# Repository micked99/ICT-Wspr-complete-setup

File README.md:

## Updates
20261018  <br>
Changed Timing.h so it will not wait for its 10 min schedule, if the board starts at any minute inside the scheduled time it will starta at next 2 min window to tx a standard wspr packet and then resume the order of schedule you have set.

20261017  <br>
Major overhaul of the code, biggest enhancements is the mergin of the 180° tx code with the normal tx code with a setting to run the board in standard - normal (true/false flag) dipole mode or in 180° mode with the dipole halfs fed 180° antiphase, quadruple the power output but only doubling the power consumption of the si5351 - in theory. Power demands increase from 25mA in dipole to 30mA 180 degree mode, also lots of old unused code mainly the jt9 codesnips that was left in there removed, all user configureble  settings moved to one place in the beginning of the .ino file - new and old pcb:s 100% compatible but old pcb:s does not have clk1 routed that is needed for 180° tx so only dipole mode works on them. (si5351 use about 17mA in stb and 27mA in tx using clk0 + 5mA for clk1.) <br>
Bugfix: if slot on minute 8 was used in previous fw it jumped a 10min seq before it started tx again - now been fixed <br>

Fixed a bug in telemetry/gps data and moved all configurable settings into the .ino file, like channel and tcxo freq

A 180° tx with a 4x power output avalible here: https://github.com/micked99/ICT-wspr-180-4x-the-power-output

BOM and Pick and place files added if you want to for example JLCPCB to make and assamble the complete board  

BOM_ict_v361-xs.csv & CPL_pick place_ict_v361-xs.xlsx  

Screenshots of the settings of order of pcb assembly, see folder "JLCPcb order"  

Get your board online onto Sondehub/aprs.fi section added  

# ICT-v7-ATGM336
  <br> <br>

## Introduction
This FW is mostly the work of Eduard YO3ICT,  you can read about here: https://yo3ict.uus.ro/tracker.html  
What I have done is to simplify it even more with a few less components and a slightly easier to solder pcb.

What Eduard did was reverse enginer the [QRP-Labs](https://shop.qrp-labs.com) telemetry protocol which use wspr to get data through, and open sourced it, details of the protocol is described here: https://qrp-labs.com/flights/s4#protocol 
most balloons use this encoding today, with a few exceptions, like [Zachtek](https://www.zachtek.com)  

Another good site for beginers is to read up and join the io board at: https://groups.io/g/picoballoon 

The [Traquito](https://traquito.github.io/)  page will host channel reservation and upload to varous tracking sites like https://aprs.fi/ and https://amateur.sondehub.org/ and as well host its own map, more maps and info avalible here https://lu7aa.org/dx.asp and here http://qrp-labs.com/tracking.html, another good page that poped up lately is [wsprtv](https://wsprtv.com/docs/user_guide.html#u4b-channel-map) & [wsprtv channel map](https://wsprtv.com/tools/channel_map.html?band=17m&num_days=30&rx_threshold=1)

##
## --Everything in this git is in Metrics--
##

## Folders in this repo:  
### ICT_WSPR   
The Arduino code to upload to the PCB  
### Libraries
Copy the content in this folder into libraries folder of Arduino C:\Program Files (x86)\Arduino\libraries  
### Pcb-ICT-main  
Cam files for pcb ordering as well as the Eagle schematic and board files, viewer for both files here: https://www.altium365.com/viewer/
### Boards.txt-main  
Replace the Boards.txt in arduino to controll the speed of the 328, its located in: C:\Program Files (x86)\Arduino\hardware\arduino\avr  

## Goals  
This setup is aimed at three main things: light weight, low power demands and as few components as possible - easy to build

The board can be built to weigh below 1 gram fully assembled (pic below) with solar cells & antenna connected total weight 4-5 gram

To make the board consume as little power as possible its setup to switch between tx and gps so only one of the two is ON at any time, so it will startup and get valid gps lock with tx side of the board switched off, the tx ic - si5351 consumes 17-27mA (depending on model) in stb curent even when not in use so only the gps is on and draws about 25mA using the ATGM336 (N31), when the board have got a valid lock the gps will turn off and the wspr tx starts, it will be about 30mA, on top of this the 328 running at 2Mhz and the Tcxo combined will take another 3mA 

The board will work on any band between 14Mhhz and 28Mhz

# Features  
CW init - At power on, when sun hits the solar panels it start to tx cw, then you know you are good for launch  
No tx over selected grids - Move tx to ism (13.555) freq over selected grids  
Powerswitching between gps and tx - Will put less stress on the cells and get earlie in the morning startups  
Course altitude in main wspr - Will insert a rough altitude into the standard wspr db field, see TelemFunctions.h  
Good WDT function of 328 - Will never fail to wake up even with unstable solar cells powering the board  
Will work at low clocks, tested down to 1Mhz on the 328 - Deafult is 2Mhz  
Powersave of gps by set it to single navigational system  - See Gps section  

# GPS:

The ATGM336-N31 support both GPS and Beidou system, by switching off Beidou and run the ATGM in GPS only mode we save about 4mA, see .ino file for the command, gps only is activated by default.  
This gps does not have any altitude limit like many other modules, its been tested to 150.000m with a hack-rf and GPSSim and still worked fine

## BOM

All components but the si5351 is bought on Aliexpress, you can source the SI535/MS5351 on Ali but they can have an higher power consumption then the original, from my experience the Ali ones draw 27mA instead of 17mA in stb current of the genuine ones 
----------------  
Cpu ATmega328P (328PB also works but need installing MiniCore in Arduino IDE)

Gps ATGM336 (N31) others will work  

TX Si5351  

Tcxo 25/26/27 Mhz size 3225 3.2x2.5mm  

Xo 4Mhz size 4520 4.5mm×2mm   

2x 10K resistor size 0603, value non critical, 1K-10K works  

2x 100nF Capacitor size 0603, value non critical 10-470nF works, it will work fine without any soldered on but I recommend at least one  

2.54mm x2 Pin Header - Remove before flight by cutting it of with a scissor  

# Antennas

For gps antenna use a 46mm wire which represents a 1/4 antenna at 1575Mhz  

For tx antenna I use 0,15mm which is a good combination of strength and weigh but any wire in the 0,1 - 0,2mm will work fine, try enameled copper wire that is heatstrippable

I use a small hook 2cm long made of 0,6mm wire bottom, and 0,8mm at the top to solder on the antenna wire, solder and twist a couple of turns arround the hook  
  <br>  
Here is good picture where you can see the Red and Yellow gps antennas  
  <br>  

Tx Antenna length calculated as normal, 300/freq x 0.95 /4 

Upper antenna leg should be supported by a fishing line taped between the balloon and pcb

# Solar cells

6 psc of solar cells connected in series will work fine, or 4 psc of a bit larger cells and a voltage doubler with 3,3V ldo like REG710 will do the work, ready made pcb are avalible on Aliexpress, search for "Low Noise Regulated Charge Pump" see below pic  
  <br> 

Do not try use converters with an inductor, they will not work, only converters using a capacitor are likeley to succeed.  

As can be seeen in the below picture the solar cells is intended to be soldered to the board with a center copper rod of 0,8mm, notice,  
there are two pairs of vias, one is GND and one pair is not connected to anything which is where you solder the center support for the cells - see below pic  
  <br>  
OBS! The programming pinhead should be cutoff before flight and preferably before you solder the cells onto the pcb  

 <br> 
Solderpoints for the solar cells  

With 6 x 38x19 cells ounded flat you can see a startup of the board at about 13° solar angle 

How I solder the cells together, I use a 0,6mm wire I extract from a multi stranded electrical cable, and then a very thin wire from an even smaller multi stranded cable to solder the cells to the pcb, pics:

  <br>  
  <br>  

To test the solar + board indoor before a flight you can use a Halogen flood light like below pic, I use a 400W, 8545 lumen lamp.  
-OBS- Led lamps wont work.

  <br>  

# Arduino

To compile and upload the sketch I use Arduino version 1.8.13 which you find here, others will work but not tested, <br> https://www.arduino.cc/en/software/OldSoftwareReleases/<br> 
Resently tested last version as of now 2.3.10 which also worked fine.

# 328 Fuses

Sets the expected external or internal xo used and also set the brownout to 1,8V

The 328 have an internal xo at 8Mhz, you can set it to be divided down by 8 (fuse) and then the board runs at 1Mhz
the internal xo at 8Mhz is not very stable in cold and it will not work at flying altitude, but I have tried a few flights on the internal xo divided down to 1Mhz 
and it have worked fine, anyway, both speeeds works fine for testing a board on the bench, but I do recomend that you use the suggested 4Mhz xo as in the schematic.

FD D9 FE 1,8V / External 2/4/8Mhz xo, Brownout to 1,8V - This is the fuses you should use if you build this board  

62 D9 FE 1.8V / internal 8Mhz osc /div8 = 1Mhz  
E2 D9 FE 1.8V / internal 8Mhz osc  

To set fuses use Avrdudess https://github.com/ZakKemble/AVRDUDESS

Fusecalc page https://www.engbedded.com/fusecalc/

I would recommend to buy a couple of arduino nano boards to practice on before flashing fuses onto a built board, as this is the main culprit of non responsive 328 - wrongly set or corrupted fuses

# Programming

The pcb is fited with a 6 pin ISP connector  
The Arduino uploads the fw with an USBasp programmer, get a 3,3v version with a 10 to 6 pin header adapter on the end of the ribbon cable  
To upload a .hex file like the one supplied in oscillator-main folder I recommend using AVRDUDESS - A GUI for AVRDUDE

https://blog.zakkemble.net/avrdudess-a-gui-for-avrdude/  
https://github.com/avrdudes/avrdude/  

Use libsusbK in Zadig to install driver for the Usbasp: https://zadig.akeo.ie/

  <br>  

In Arduino IDE select Usbasp as programmer:    
  <br>

In Boards select rAVA 2Mhz:    
  <br>  
# PCB  

  <br>  

I have always used Jlcpcb at https://jlcpcb.com/ for my balloon boards and other projects

The pcb files have been made with Eagle pcb nowadays under the name Autodesk Eagle https://www.autodesk.com/products/eagle/overview

Make the PCB as thin as possible to save weight, 0,6mm is good compromise between weight and price

In Pcb-ICT-main folder in this repo you will find needed CAM files in the zip´s, if you are a experieced with solder small parts and have a hot air solder station go with the Xtra Smal QFN version (ict_v361-xs.zip) of the board, for a more simple soldering setup use the TQFP version (ict_v361.zip)

Here is what a JLC-PCB assambled board looks like, pictures from Michael KC3GMG  

# Schematic  

# Setup parameters in the code  
The Arduino code is setup from start to use a 26Mhz Tcxo and a 4Mhz crystal, if other values used the code needs to be changed - see below  

Values to edit in the ino file  <br>

<br>

const char call[] = "SA7BSS";      // WSPR Standard callsign -- SA7BSS for bench testing, SA6BSS for flight<br>
char tlm_channel1 = '1';           // Telemetry channel: 0/1/Q<br>
char tlm_channel2 = '1';           // Telemetry channel: 0-9<br>
const uint32_t tcxo  = 26000000UL; // TCXO/crystal frequency in Hz<br>
const bool use180deg = false;      // Hardware config: true = 180° dipole (CLK0+CLK1), false = standard/ground-wire (CLK0)<br><br>
 
See this page for channel setup and reservation: https://traquito.github.io/channelmap/ & https://wsprtv.com/tools/channel_map.html

CW setup, the board will at first moment at power on send a morse signal with your callsign<br>
This is a first good test the board is working, set the freq in Beep.h, it will beep without a gps soldered
Here is my SA6BSS call in the ino file  <br>
cw_s(); cw_a(); cw_6(); cw_b(); cw_s(); cw_s();  <br>

Testing and Scheduling of tx sequence<br>

After power on it will beep a cw for 5 sec then switch over to gps that takes about 25-30sec to get a GPS fix if in clear sky or gps repeater used, GPS through a window can take 1-2 minutes.

Edit Timing.h sceduling at what minute you want to tx your normal wspr and at what minute to tx the telemetry, this can be done inside Arduino ide or with a normal texteditor, this is self explanatory

const uint8_t TX_SLOTS  = SLOT(0) | SLOT(2) | SLOT(6) | SLOT(8);  // minutes that transmit; any other even minute is idle (GPS only)<br>
const uint8_t TLM_SLOT  = 2;   // minute that carries the telemetry message (must be one of TX_SLOTS)<br>
const uint8_t PREP_SLOT = 6;   // minute where new GPS data is read (the first TX slot after the idle one)<br>

"PREP_SLOT = 6; "This can be a bit unlogical but its the first tx after the GPS got new data, we can see "TX_SLOTS  = SLOT(0) | SLOT(2) | SLOT(6) | SLOT(8); " where 4 is the slot where the radio switch off and the gps enables, so PREP_SLOT = 6; is the first slot after gps got new data into the board

To adjust the sequence in what order the standard and telemtry is transmitted edit Timing.h, it is set to transmitt 4 times - 8 minutes and then switching off the radio and enable gps, gets new loction data, then start over.

##

This is the standard setup using a 4 Mhz xo, so if you build the board with the recommended components and downloaded fw this does not need to change
Sets speed of the board  
clock_prescale_set(clock_div_2);  or clock_prescale_set(clock_div_4);  
this in conjuction with:    
#define WSPR_CTC 1334  
and select rAVA 2Mhz from boards in Arduino boards 

Alternative clocksettings:  
WSPR CTC - 2668 @ 4Mhz //1334 @ 2Mhz //667 @ 1Mhz  
And to select the appropriate board setting under Boards in Arduino,  
lets say we want to set the board to 1Mhz using a 4Mhz xo we need to set the prescaler to  
clock_prescale_set(clock_div_4);   
and set  
WSPR CTC 667  
and then select gAVA 1Mhz under boards, see section Programming  

then, for example if you wan to run it a 4Mhz set:
WSPR CTC - 2668  
mark out both of the //clock_prescale_set  
and use hAVA 4Mhz board setting  

to set cw tx frequncy adjust it in Beep.h, this will tx a short cw init as soon as you connect power<br>
     freq = 14096980UL;  <br>
  // freq = 18105900UL;  <br>
  // freq = 28125870UL;  <br>

# Balance the board

You want the board to be as leveled as possible so the solarcells always points up and not to the sides,  
to do this use the top hook, puti it on a short loop of fishing line and bend the copper rod untill it levels up, see below:  

  <br> 

# Get your flight uploaded to Sondehub and/or aprs.fi

There is a couple of ways to get your board onto [Sondehub](https://amateur.sondehub.org/) 

The way Im doing it is to use a wspr-to-sondehub python script described here: https://github.com/micked99/wspr-to-sondehub-script
What I do is to use this script with a filtering function so your upload data dont get mixed with other flights - you should check the channel is free here before relesing a balloon:  [WSPR-TV](https://wsprtv.com/tools/channel_map.html?band=17m&num_days=30&rx_threshold=1) but as the 600 channels per band is relaying on filtering on frequency and this script cant handle that, this is a simple workarround.
So the idea I got and that DG4NOB implemented in the python upload code was that we can use the voltage reading of the battery as a filtering function, as we use solar cells, voltage is mostly of no interest, reading the Encoding [Description](https://qrp-labs.com/flights/s4#protocol) we see "Battery voltage is coded by a number in the range 0..39, which represents battery voltage in the range 3.00 to 4.95V with a resolution of 0.05V" this means we have 40 unique "channels" within this, so what we can do is to set a static value in the ict fw and uplod this to the board, <br> 
look at lines 126 - 132 in TelemFunctions.h and you see this:<br> 

  sensorVolt = sensorVolt / 5;   // mark out for fixed voltage<br> 
  volt = sensorVolt * 1.1f;      // mark out for fixed voltage<br> 
  volt = volt / 1023.0f;         // mark out for fixed voltage<br> 
  volt = volt * 4.18f;           // mark out for fixed voltage<br> 
  // volt = 3.94;                // --Remove if sensor voltage is used--<br>
  if (volt < 3.0) volt = 3.0;    // mark out for fixed voltage<br>
  if (volt > 4.95) volt = 4.95;  // mark out for fixed voltage<br>   

The normal setup is as above where the adc reads the voltage on sensorpin, it should be a voltage divider there but I have routed the pin directly to vcc so if you dont make any edits to the code it will constantly read 4.56V, so what we can do is to change the code, say we want to filter the voltage to 3,94V we edit the code to:  

 // sensorVolt = sensorVolt / 5;   // mark out for fixed voltage<br>
 // volt = sensorVolt * 1.1f;      // mark out for fixed voltage<br>
 // volt = volt / 1023.0f;         // mark out for fixed voltage<br>
 // volt = volt * 4.18f;           // mark out for fixed voltage<br>
    volt = 3.94;                   // --Remove if sensor voltage is used--<br>
 // if (volt < 3.0) volt = 3.0;    // mark out for fixed voltage<br>
 // if (volt > 4.95) volt = 4.95;  // mark out for fixed voltage<br>

After we done this and upload the code to the pcb we should have a fixed voltage reading constantly sending 3,94V which we can put in the balloon.ini file in the  [wspr upload script](https://github.com/micked99/wspr-to-sondehub-script)  

If you have launched the board with no editing to the ict code you can set 4,56V as a filter, this making it work on boards allready in flight.  

You need to double check the voltage readign your board actually tx as there will be a 0,01V variation on the actual value that comes out of the decoder, even if you set 3,94V it might be 3,95 that comes out, you can test it in this xls  
https://qrp-labs.com/images/ultimate3builder/ve3kcl/s4/308d.xls  
originating from https://qrp-labs.com/flights/s4#protocol  

Other ways to get you board online is to use https://lu7aa.org.ar/wsprset.asp  

There is also an uploader by Bill WB8ELK - maker of [Skytracker](https://elktronics.com) that you can download from [Here](https://groups.io/g/picoballoon/message/23150?p=%2C%2C%2C50%2C0%2C0%2C0%3A%3Arecentpostdate%2Fsticky%2C%2Cwspr2aprs%2C50%2C2%2C0%2C114107378)  
You need to be a member of this io board to access it, it will upload to aprs.fi and Sondehub will then automaticly pipe it onto its site,  
pros of this program is easy to setup and it can filter on Frequency as the 600 channel mapping require.  

# Misc pictures

  <br> 
  <br>

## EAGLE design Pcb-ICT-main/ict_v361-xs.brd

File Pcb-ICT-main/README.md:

# ICT-PCB

Eagle PCB for my modified version of the ICT wspr setup 

This pcb is made and setup for my current version of the the ict code

ict_v361-xs // Extra small, using the QFN/MLF version of the 328 - Verified working

ict_v361 // Normal size, using the TQFP version of the 328 - untested but should work

Use .zip files for pcb ordering

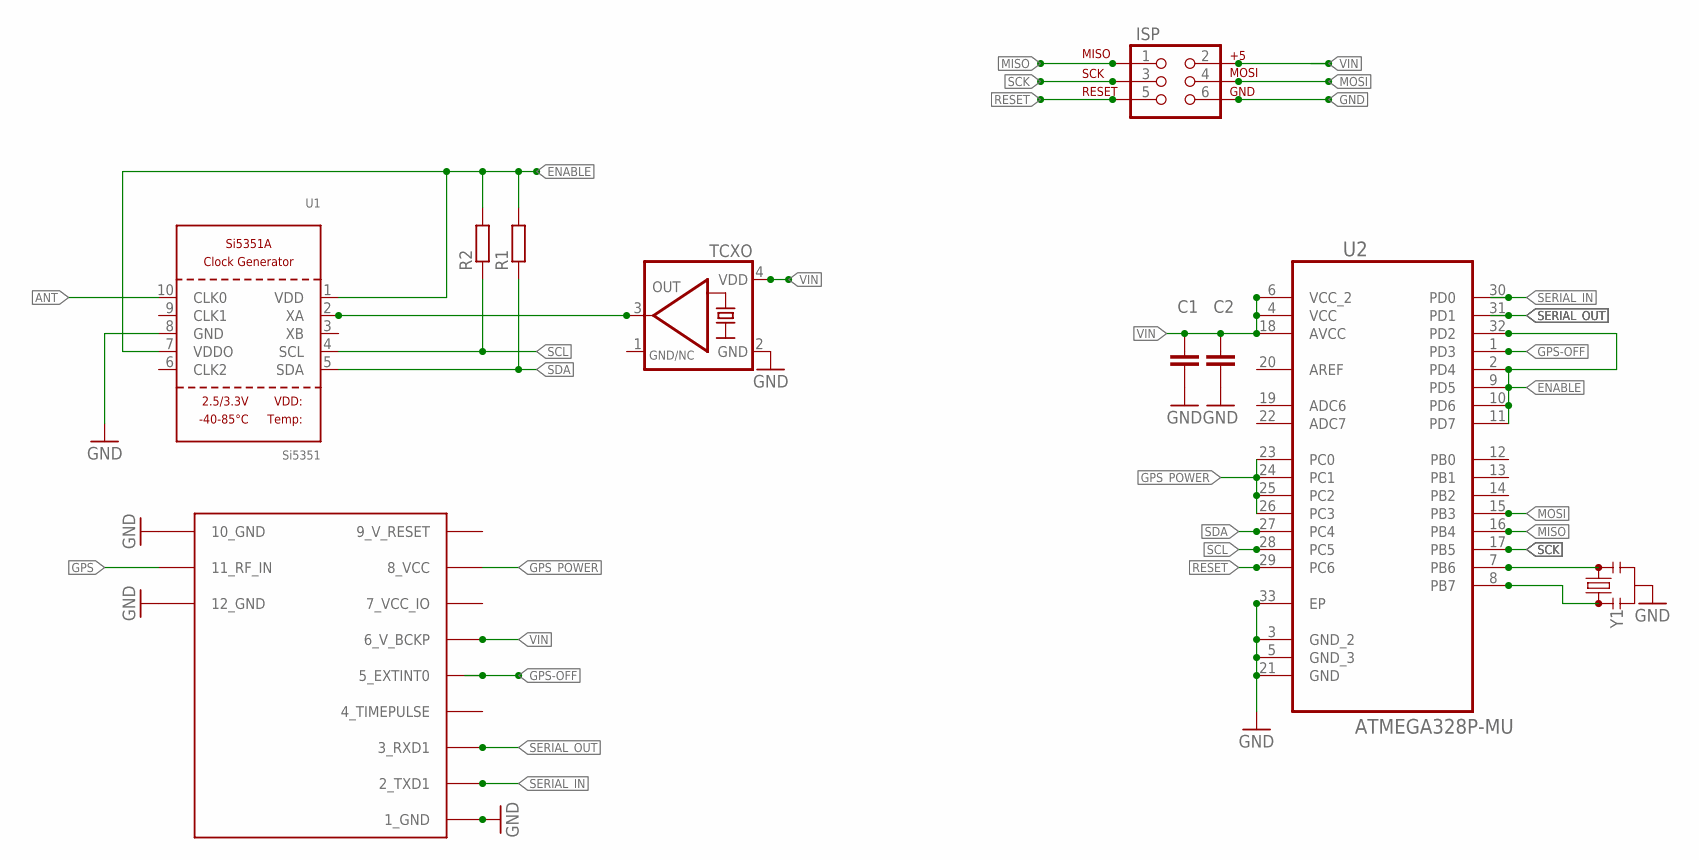
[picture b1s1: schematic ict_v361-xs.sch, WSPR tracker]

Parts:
C1, C2: C-EUC0603K; C0603K
GPS: UBLOX_MAX
ISP: AVR_SPI_PRG_6PTH; 2X3
R1, R2: R-EU_R0603; R0603
TCXO: KXO-TCXO-CMOS-84; 3.2X2.5_KXO-84-TCXO
U1: Si5351; MSOP10
U2: ATMEGA328P-MU; QFN50P500X500X100-33N
Y1: RESONATORSMD-4.5X2.0; RESONATOR-SMD-4.5X2.0

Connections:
7_VCC_IO: GPS.7_VCC_IO
9_V_RESET: GPS.9_V_RESET
ANT: U1.10 (CLK0)
ENABLE: R1.2, R2.2, U1.1 (VDD), U1.7 (VDDO), U2.2 (PD4), U2.9 (PD5), U2.10 (PD6), U2.11 (PD7), U2.32 (PD2)
GND: C1.2, C2.2, GPS.1_GND, GPS.10_GND, GPS.12_GND, ISP.6, TCXO.2 (GND), U1.8 (GND), U2.3 (GND_2), U2.5 (GND_3), U2.21 (GND), U2.33 (EP), Y1.2
GND/NC: TCXO.1 (GND/NC)
GPS: GPS.11_RF_IN
GPS-OFF: GPS.5_EXTINT0, U2.1 (PD3)
GPS_POWER: GPS.8_VCC, U2.23 (PC0), U2.24 (PC1), U2.25 (PC2), U2.26 (PC3)
MISO: ISP.1, U2.16 (PB4)
MOSI: ISP.4, U2.15 (PB3)
unnamed: U2.7 (PB6), Y1.3
unnamed: U2.8 (PB7), Y1.1
unnamed: TCXO.3 (OUT), U1.2 (XA)
RESET: ISP.5, U2.29 (PC6)
SCK: ISP.3, U2.17 (PB5)
SCL: R2.1, U1.4 (SCL), U2.28 (PC5)
SDA: R1.1, U1.5 (SDA), U2.27 (PC4)
SERIAL_IN: GPS.2_TXD1, U2.30 (PD0)
SERIAL_OUT: GPS.3_RXD1, U2.31 (PD1)
VIN: C1.1, C2.1, GPS.6_V_BCKP, ISP.2, TCXO.4 (VDD), U2.4 (VCC), U2.6 (VCC_2), U2.18 (AVCC)

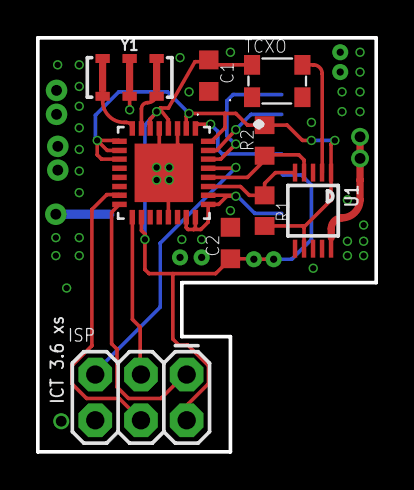
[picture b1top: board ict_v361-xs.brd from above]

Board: 2 copper layers, 18.8 x 23.0 mm, 10 parts (1 on the bottom side), 16 nets.

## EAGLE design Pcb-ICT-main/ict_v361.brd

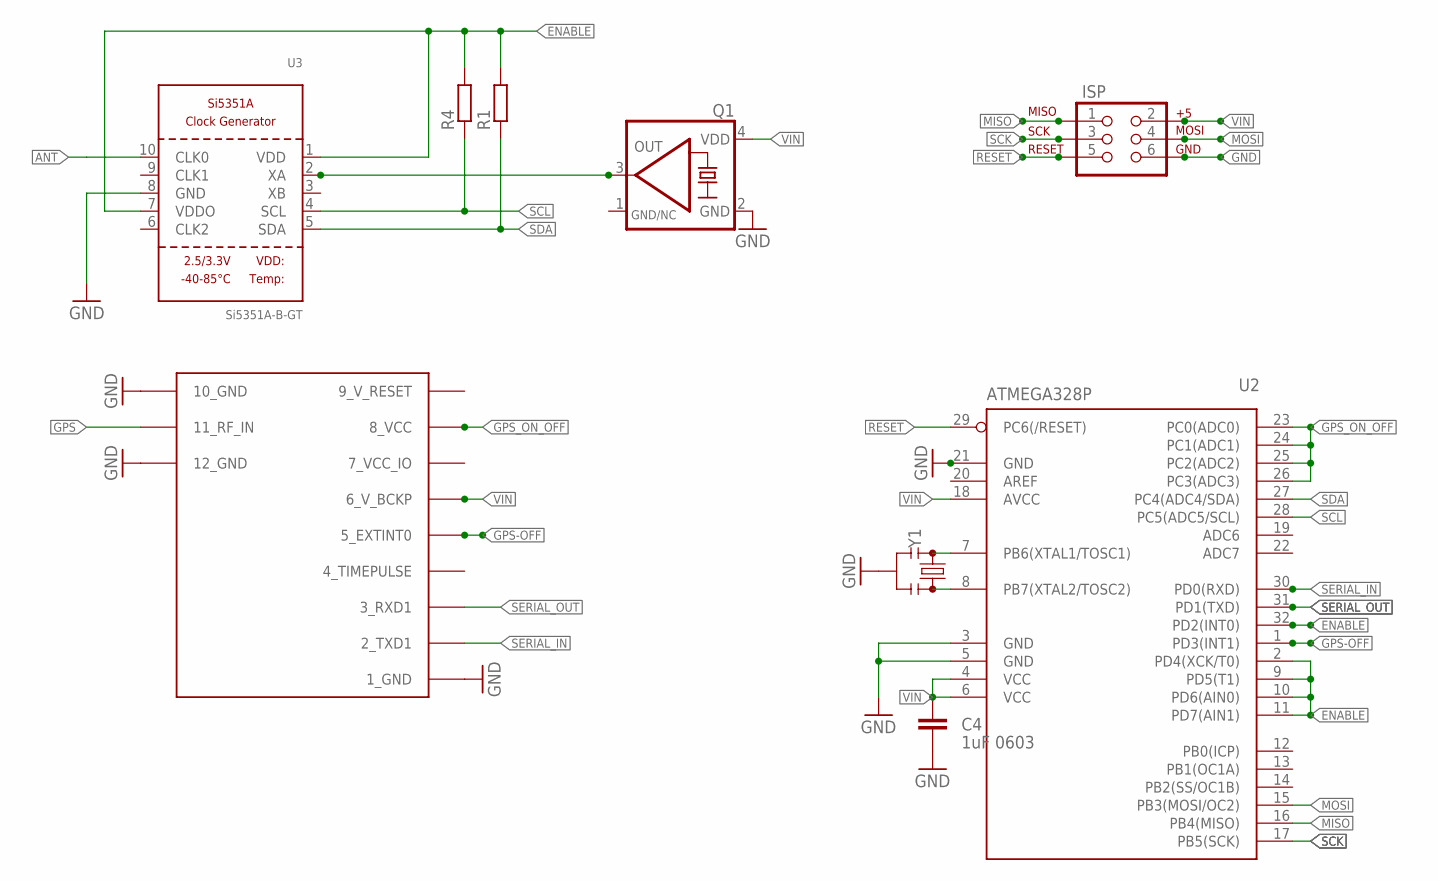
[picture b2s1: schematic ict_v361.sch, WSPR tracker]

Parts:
C4: 1uF 0603; C0603K
ISP: AVR_SPI_PRG_6PTH; 2X3
Q1: KXO-TCXO-CMOS-84; 3.2X2.5_KXO-84-TCXO
R1, R4: R-EU_R0603; R0603
U2: ATMEGA328P; TQFP32-08
U3: Si5351A-B-GT; MSOP10
U$2: UBLOX_MAX
Y1: RESONATORSMD-4.5X2.0; RESONATOR-SMD-4.5X2.0

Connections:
7_VCC_IO: U$2.7_VCC_IO
9_V_RESET: U$2.9_V_RESET
ANT: U3.10 (CLK0)
ENABLE: R1.2, R4.2, U2.2 (PD4(XCK/T0)), U2.9 (PD5(T1)), U2.10 (PD6(AIN0)), U2.11 (PD7(AIN1)), U2.32 (PD2(INT0)), U3.1 (VDD), U3.7 (VDDO)
GND: C4.2, ISP.6, Q1.2 (GND), U2.3 (GND), U2.5 (GND), U2.21 (GND), U3.8 (GND), U$2.1_GND, U$2.10_GND, U$2.12_GND, Y1.2
GND/NC: Q1.1 (GND/NC)
GPS: U$2.11_RF_IN
GPS-OFF: U2.1 (PD3(INT1)), U$2.5_EXTINT0
GPS_ON_OFF: U2.23 (PC0(ADC0)), U2.24 (PC1(ADC1)), U2.25 (PC2(ADC2)), U2.26 (PC3(ADC3)), U$2.8_VCC
MISO: ISP.1, U2.16 (PB4(MISO))
MOSI: ISP.4, U2.15 (PB3(MOSI/OC2))
unnamed: U2.8 (PB7(XTAL2/TOSC2)), Y1.3
unnamed: U2.7 (PB6(XTAL1/TOSC1)), Y1.1
unnamed: Q1.3 (OUT), U3.2 (XA)
RESET: ISP.5, U2.29 (PC6(/RESET))
SCK: ISP.3, U2.17 (PB5(SCK))
SCL: R4.1, U2.28 (PC5(ADC5/SCL)), U3.4 (SCL)
SDA: R1.1, U2.27 (PC4(ADC4/SDA)), U3.5 (SDA)
SERIAL_IN: U2.30 (PD0(RXD)), U$2.2_TXD1
SERIAL_OUT: U2.31 (PD1(TXD)), U$2.3_RXD1
VIN: C4.1, ISP.2, Q1.4 (VDD), U2.4 (VCC), U2.6 (VCC), U2.18 (AVCC), U$2.6_V_BCKP

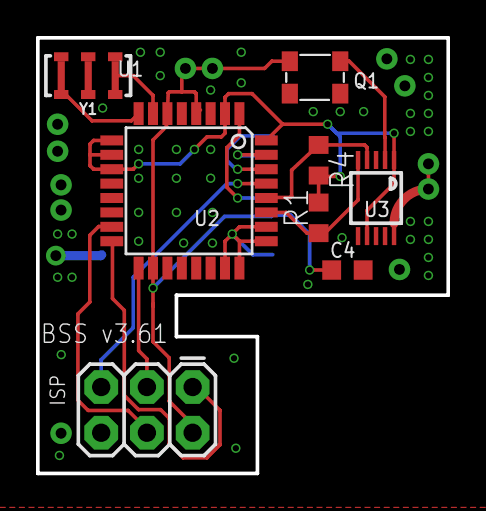
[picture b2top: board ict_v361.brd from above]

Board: 2 copper layers, 22.8 x 24.2 mm, 9 parts (1 on the bottom side), 16 nets.

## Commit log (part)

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2025-10-23 Adjusted C1 placement

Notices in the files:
parts and their libraries:
microbuilder: This work is placed in the public domain, and may be freely used for commercial and non-commercial work with the following conditions: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
crystal-geyer_V1_0: Copyright: Geyer-Electronic
